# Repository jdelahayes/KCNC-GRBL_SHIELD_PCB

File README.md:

KCNC GRBL SHIELD 

Ceci est un shield GRBL pour Arduino Uno adapté à la R-CNC (makerfr.com).

TODO
Elargir les pads à 2.54mm pour permettre l'utilisation de rivets de 1.4mm (la tete mesure dans ce cas 2.35mm) sur :
 - les borniers à vis 2 et 3 points;
 - le regulateur 7805
 - les condensateurs polarisés

Nettoyer les angles des pistes.

Réduire le longeur de la carte pour avoir une marge sur les plaque présensibilisées au format 160x100mm

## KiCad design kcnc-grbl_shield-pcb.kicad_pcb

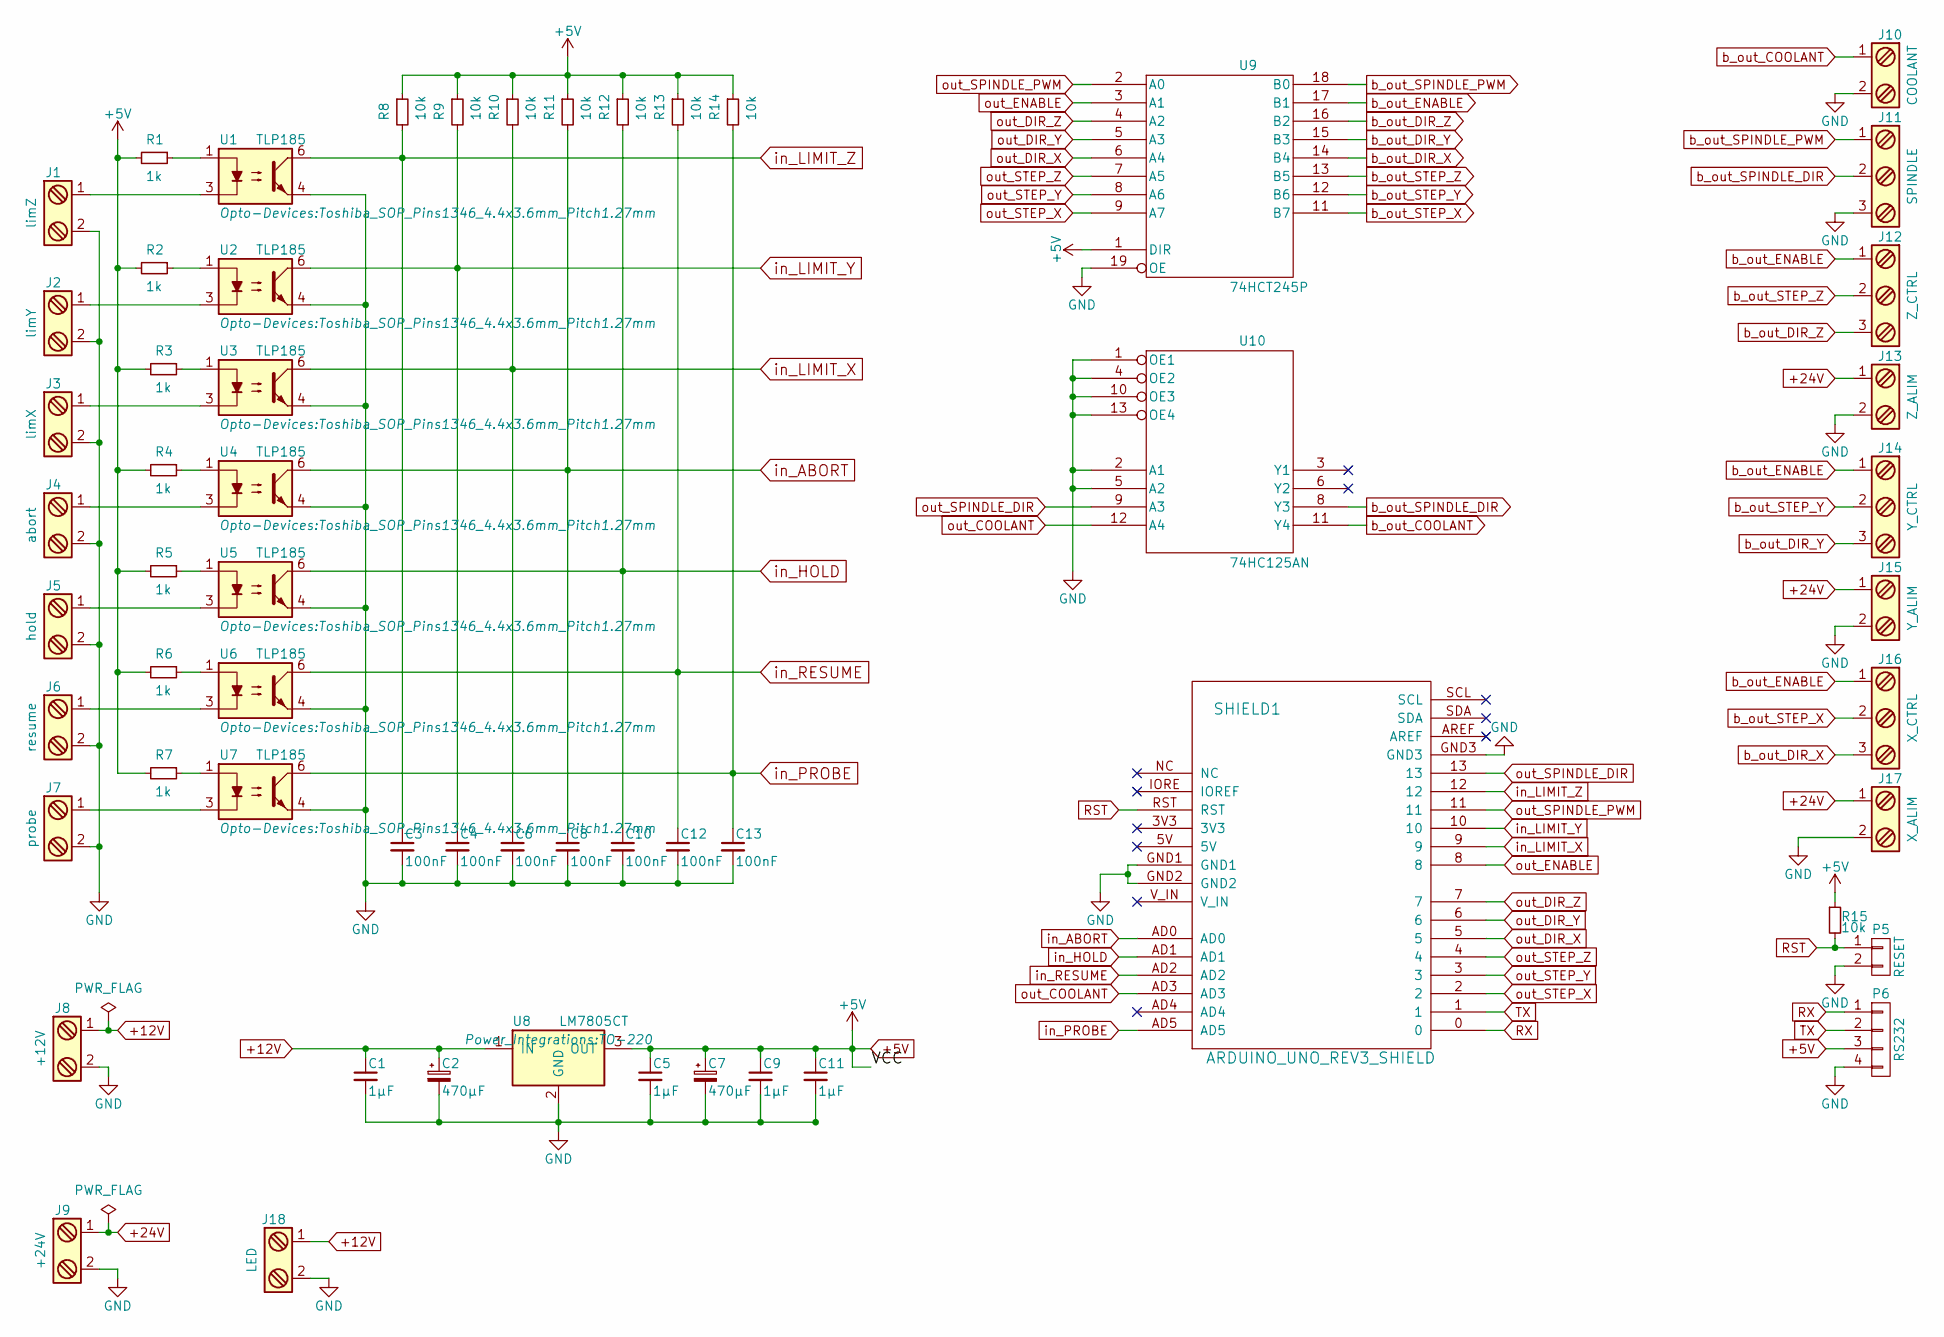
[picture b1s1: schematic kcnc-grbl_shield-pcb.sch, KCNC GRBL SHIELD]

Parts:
C1, C5: 1µF; C_0805
C2, C7: 470µF; CP_Radial_D8.0mm_P2.50mm
C3, C4, C6, C8, C10, C12, C13: 100nF; C_0603
C9, C11: 1µF; C_0603
J1: limZ; screw_terminal_3.5mm_pitch_2p
J2: limY; screw_terminal_3.5mm_pitch_2p
J3: limX; screw_terminal_3.5mm_pitch_2p
J4: abort; screw_terminal_3.5mm_pitch_2p
J5: hold; screw_terminal_3.5mm_pitch_2p
J6: resume; screw_terminal_3.5mm_pitch_2p
J7: probe; screw_terminal_3.5mm_pitch_2p
J8: +12V; screw_terminal_3.5mm_pitch_2p
J9: +24V; screw_terminal_3.5mm_pitch_2p
J10: COOLANT; screw_terminal_3.5mm_pitch_2p
J11: SPINDLE; screw_terminal_3.5mm_pitch_3p
J12: Z_CTRL; screw_terminal_3.5mm_pitch_3p
J13: Z_ALIM; screw_terminal_3.5mm_pitch_2p
J14: Y_CTRL; screw_terminal_3.5mm_pitch_3p
J15: Y_ALIM; screw_terminal_3.5mm_pitch_2p
J16: X_CTRL; screw_terminal_3.5mm_pitch_3p
J17: X_ALIM; screw_terminal_3.5mm_pitch_2p
J18: LED; screw_terminal_3.5mm_pitch_2p
P5: RESET; Pin_Header_Straight_1x02_Pitch2.54mm
P6: RS232; Pin_Header_Straight_1x04_Pitch2.54mm
R1, R2, R3, R4, R5, R6, R7: 1k; R_0603
R8, R9, R10, R11, R12, R13, R14, R15: 10k; R_0603
SHIELD1: ARDUINO_UNO_REV3_SHIELD; KCNC_GRBL_SHIELD
U1, U2, U3, U4, U5, U6, U7: TLP185; Toshiba_SOP_Pins1346_4.4x3.6mm_Pitch1.27mm
U8: LM7805CT; TO-220
U9: 74HCT245P; SSOP-20
U10: 74HC125AN; SOIC-14_N

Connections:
+5V: C5.1, C7.1, C9.1, C11.1, P6.3, R1.2, R2.2, R3.2, R4.2, R5.2, R6.2, R7.2, R8.1, R9.1, R10.1, R11.1, R12.1, R13.1, R14.1, R15.1, U8.3 (OUT), U9.1 (DIR), U9.20 (VCC), U10.14 (VCC)
+12V: C1.1, C2.1, J8.1, J18.1, U8.1 (IN)
+24V: J9.1, J13.1, J15.1, J17.1
GND: C1.2, C2.2, C3.2, C4.2, C5.2, C6.2, C7.2, C8.2, C9.2, C10.2, C11.2, C12.2, C13.2, J1.2, J2.2, J3.2, J4.2, J5.2, J6.2, J7.2, J8.2, J9.2, J10.2, J11.3, J13.2, J15.2, J17.2, J18.2, P5.2, P6.4, SHIELD1.GND1, SHIELD1.GND2, SHIELD1.GND3, U1.4, U2.4, U3.4, U4.4, U5.4, U6.4, U7.4, U8.2 (GND), U9.10 (GND), U9.19 (OE), U10.1 (OE1), U10.2 (A1), U10.4 (OE2), U10.5 (A2), U10.7 (GND), U10.10 (OE3), U10.13 (OE4)
unnamed: J1.1, U1.3
unnamed: J2.1, U2.3
unnamed: J3.1, U3.3
unnamed: J4.1, U4.3
unnamed: J5.1, U5.3
unnamed: J6.1, U6.3
unnamed: J7.1, U7.3
unnamed: R1.1, U1.1
unnamed: R2.1, U2.1
unnamed: R3.1, U3.1
unnamed: R4.1, U4.1
unnamed: R5.1, U5.1
unnamed: R6.1, U6.1
unnamed: R7.1, U7.1
RST: P5.1, R15.2, SHIELD1.RST
RX: P6.1, SHIELD1.0
TX: P6.2, SHIELD1.1
b_out_COOLANT: J10.1, U10.11 (Y4)
b_out_DIR_X: J16.3, U9.14 (B4)
b_out_DIR_Y: J14.3, U9.15 (B3)
b_out_DIR_Z: J12.3, U9.16 (B2)
b_out_ENABLE: J12.1, J14.1, J16.1, U9.17 (B1)
b_out_SPINDLE_DIR: J11.2, U10.8 (Y3)
b_out_SPINDLE_PWM: J11.1, U9.18 (B0)
b_out_STEP_X: J16.2, U9.11 (B7)
b_out_STEP_Y: J14.2, U9.12 (B6)
b_out_STEP_Z: J12.2, U9.13 (B5)
in_ABORT: C8.1, R11.2, SHIELD1.AD0, U4.6
in_HOLD: C10.1, R12.2, SHIELD1.AD1, U5.6
in_LIMIT_X: C6.1, R10.2, SHIELD1.9, U3.6
in_LIMIT_Y: C4.1, R9.2, SHIELD1.10, U2.6
in_LIMIT_Z: C3.1, R8.2, SHIELD1.12, U1.6
in_PROBE: C13.1, R14.2, SHIELD1.AD5, U7.6
in_RESUME: C12.1, R13.2, SHIELD1.AD2, U6.6
out_COOLANT: SHIELD1.AD3, U10.12 (A4)
out_DIR_X: SHIELD1.5, U9.6 (A4)
out_DIR_Y: SHIELD1.6, U9.5 (A3)
out_DIR_Z: SHIELD1.7, U9.4 (A2)
out_ENABLE: SHIELD1.8, U9.3 (A1)
out_SPINDLE_DIR: SHIELD1.13, U10.9 (A3)
out_SPINDLE_PWM: SHIELD1.11, U9.2 (A0)
out_STEP_X: SHIELD1.2, U9.9 (A7)
out_STEP_Y: SHIELD1.3, U9.8 (A6)
out_STEP_Z: SHIELD1.4, U9.7 (A5)

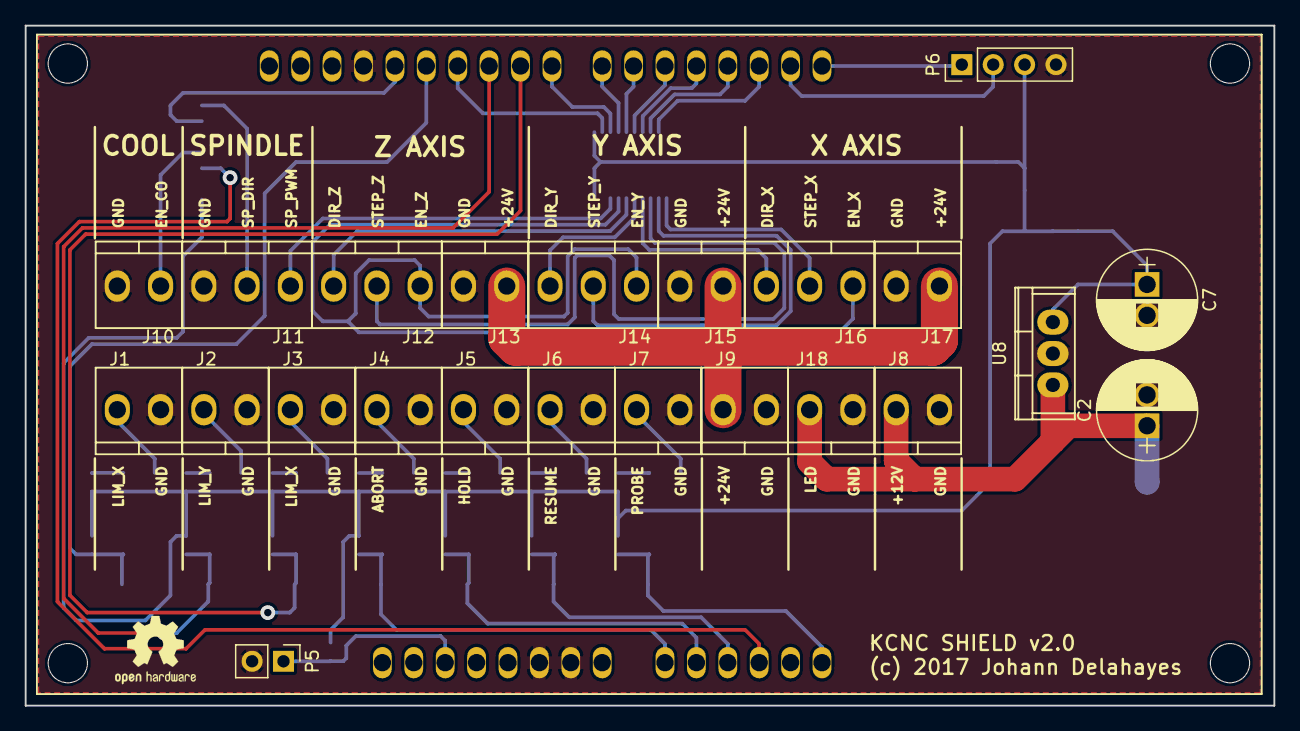
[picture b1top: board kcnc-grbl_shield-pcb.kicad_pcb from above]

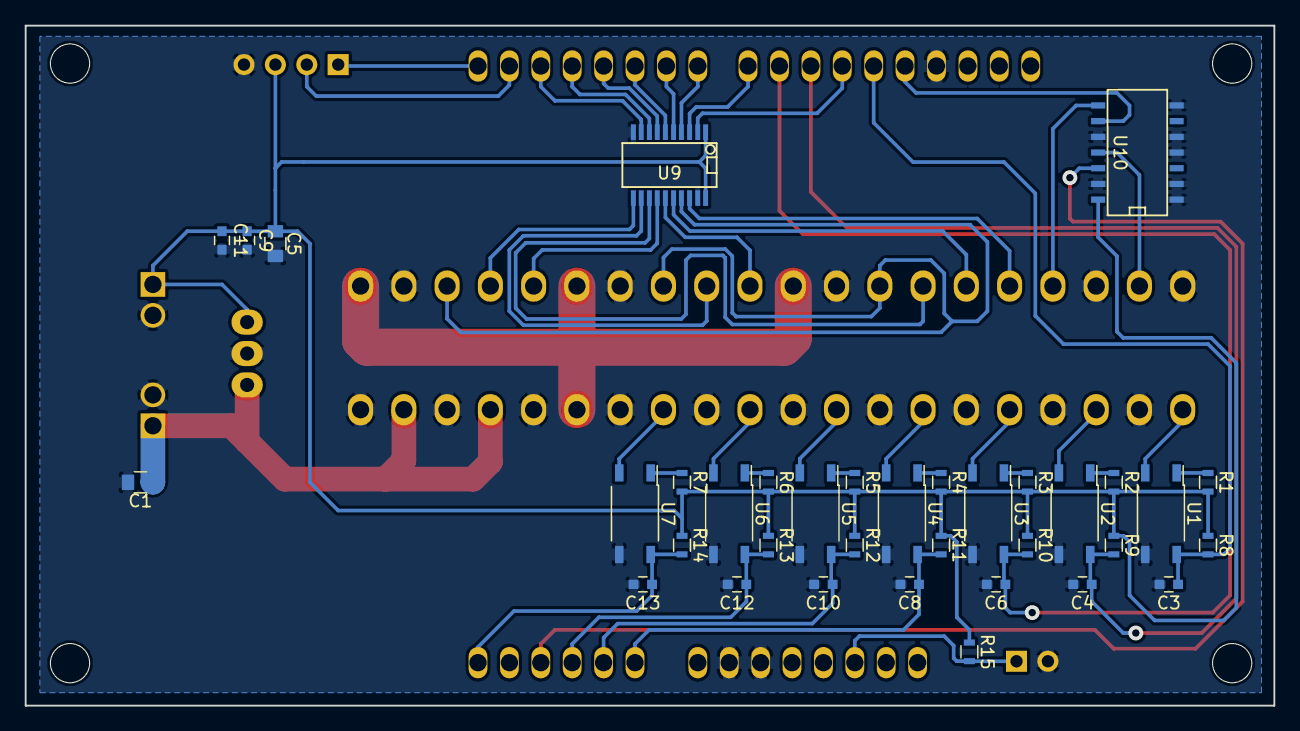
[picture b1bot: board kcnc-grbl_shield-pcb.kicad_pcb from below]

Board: 2 copper layers, 101.0 x 55.0 mm, 59 parts (35 on the bottom side), 48 nets.

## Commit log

2017-05-24 Init arduino uno grbl shield
2017-06-14 Schema v0.1
2017-06-15 Add missing files
2017-06-16 Commit V1.0
2017-06-17 V1.1
2017-06-30 Version 2
    Commit de la version 2
2017-06-30 Mise à jour du README

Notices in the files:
kcnc-grbl_shield-pcb.kicad_pcb:
(c) 2017 Johann Delahayes
